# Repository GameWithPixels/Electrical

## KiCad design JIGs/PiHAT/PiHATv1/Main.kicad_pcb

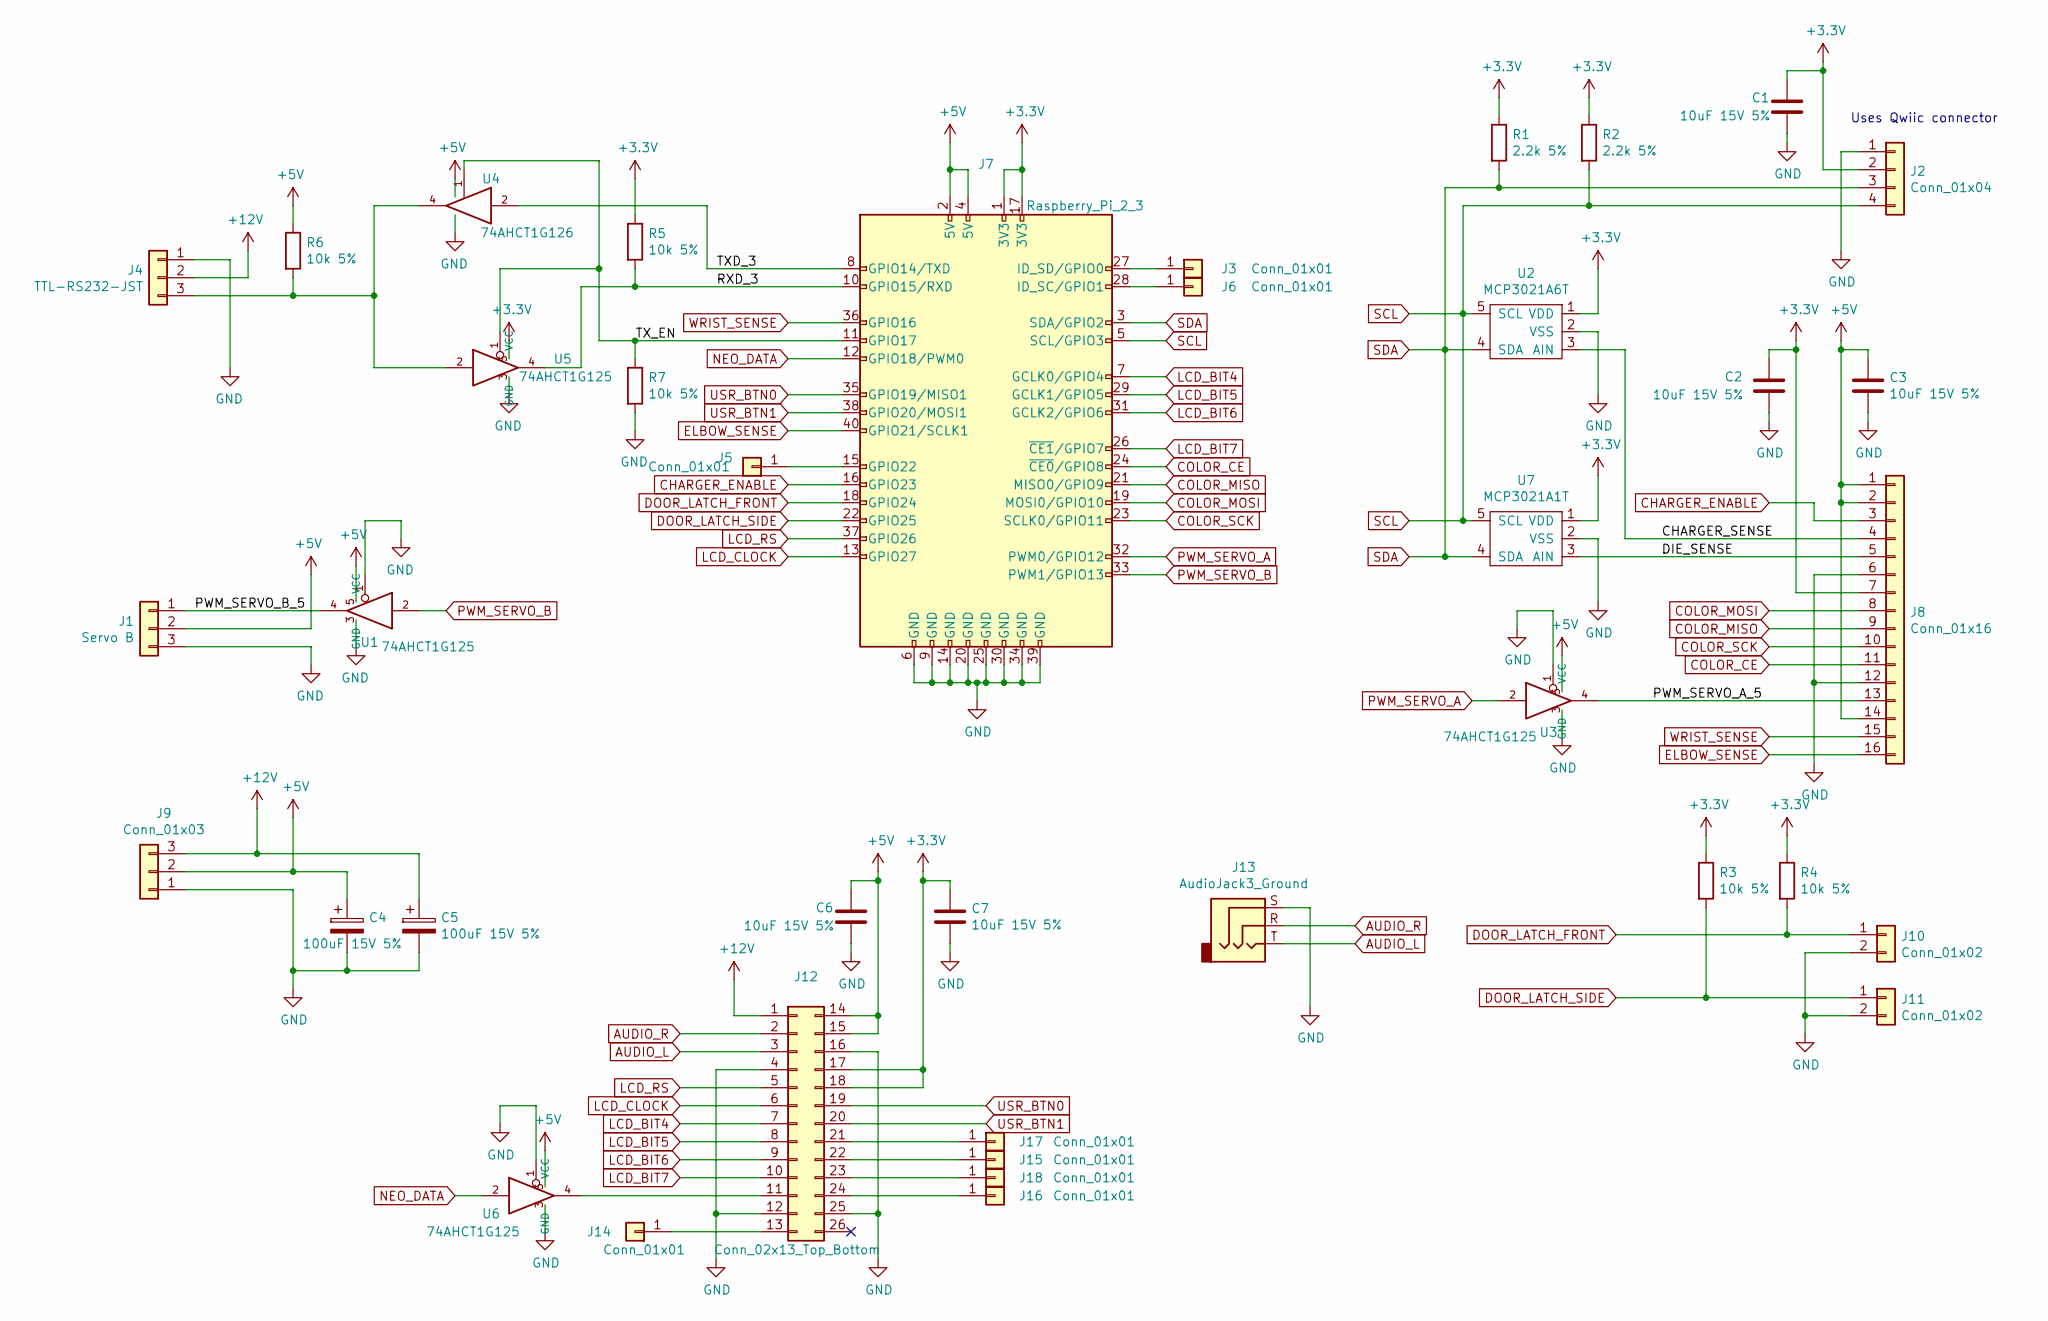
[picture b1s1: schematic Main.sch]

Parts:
C1, C2, C3, C6, C7: 10uF 15V 5%; C_0805_2012Metric; Mouser PN 81-GRM21BR61C106KE5K
C4, C5: 100uF 15V 5%; CP_EIA-7343-43_Kemet-X; Mouser PN 74-293D107X9016D2TE3
J1: Servo B; PinHeader_1x03_P2.54mm_Vertical; Mouser PN 523-G800W305018EU
J2: Conn_01x04; CCSH-W10R-XXTR-BK-A; Part Number CCSH-W10R-XXTR-BK-A
J3, J5, J6, J14, J15, J16, J17, J18: Conn_01x01; TEST_PIN
J4: TTL-RS232-JST; JST_EH_S3B-EH_1x03_P2.50mm_Horizontal; Mouser PN 538-22-05-7035
J7: Raspberry_Pi_2_3; PinSocket_2x20_P2.54mm_Vertical_SMD; Mouser PN 474-PRT-16763
J8: Conn_01x16; PinHeader_2x08_P2.54mm_Vertical_SMD
J9: Conn_01x03; JST_EH_S3B-EH_1x03_P2.50mm_Horizontal; Mouser PN 538-22-05-7035
J10, J11: Conn_01x02; JST_EH_S2B-EH_1x02_P2.50mm_Horizontal; Mouser PN 538-22-05-7025
J12: Conn_02x13_Top_Bottom; PinHeader_2x13_P2.54mm_Vertical_SMD
J13: AudioJack3_Ground; Jack_3.5mm_CUI_SJ1-3533NG_Horizontal_CircularHoles; Mouser PN 490-SJ1-3533NG
R1, R2: 2.2k 5%; R_0603_1608Metric; Mouser PN 603-RC0603FR-072K2L
R3, R4, R5, R6, R7: 10k 5%; R_0603_1608Metric; Mouser PN 603-RC0603FR-1010KL
U1, U3, U5, U6: 74AHCT1G125; SC-74A; Mouser PN 771-AHCT1G125GV125
U2: MCP3021A6T; SOT-23-5; Mouser PN 579-MCP3021A6T-E/OT
U4: 74AHCT1G126; SC-74A; Mouser PN 771-AHCT1G126GV125
U7: MCP3021A1T; SOT-23-5; Mouser PN 579-MCP3021A1T-E/OT

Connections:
+3V3: C1.1, C2.1, C7.1, J2.2, J7.1 (3V3), J7.17 (3V3), J8.7, J12.17, J12.18, R1.1, R2.1, R3.1, R4.1, R5.1, U2.1 (VDD), U5.5 (VCC), U7.1 (VDD)
+5V: C3.1, C4.1, C6.1, J1.2, J7.2 (5V), J7.4 (5V), J8.1, J8.2, J8.14, J9.2, J12.14, J12.15, R6.1, U1.5 (VCC), U3.5 (VCC), U4.5 (VCC), U6.5 (VCC)
+12V: C5.1, J4.2, J9.3, J12.1
/CHARGER_SENSE: J8.4, U2.3 (AIN)
/DIE_SENSE: J8.5, U7.3 (AIN)
/NEOPIXEL_DATA: J4.3, R6.2, U4.4, U5.2
/PWM_SERVO_A_5: J8.13, U3.4
/PWM_SERVO_B_5: J1.1, U1.4
/RXD_3: J7.10 (GPIO15/RXD), R5.2, U5.4
/TXD_3: J7.8 (GPIO14/TXD), U4.2
/TX_EN: J7.11 (GPIO17), R7.1, U4.1, U5.1
AUDIO_L: J12.3, J13.T
AUDIO_R: J12.2, J13.R
CHARGER_ENABLE: J7.16 (GPIO23), J8.3
COLOR_CE: J7.24 (~CE0~/GPIO8), J8.11
COLOR_MISO: J7.21 (MISO0/GPIO9), J8.9
COLOR_MOSI: J7.19 (MOSI0/GPIO10), J8.8
COLOR_SCK: J7.23 (SCLK0/GPIO11), J8.10
DOOR_LATCH_FRONT: J7.18 (GPIO24), J10.1, R4.2
DOOR_LATCH_SIDE: J7.22 (GPIO25), J11.1, R3.2
ELBOW_SENSE: J7.40 (GPIO21/SCLK1), J8.16
GND: C1.2, C2.2, C3.2, C4.2, C5.2, C6.2, C7.2, J1.3, J2.1, J4.1, J7.6 (GND), J7.9 (GND), J7.14 (GND), J7.20 (GND), J7.25 (GND), J7.30 (GND), J7.34 (GND), J7.39 (GND), J8.6, J8.12, J9.1, J10.2, J11.2, J12.4, J12.12, J12.16, J12.25, J13.S, R7.2, U1.1, U1.3 (GND), U2.2 (VSS), U3.1, U3.3 (GND), U4.3 (GND), U5.3 (GND), U6.1, U6.3 (GND), U7.2 (VSS)
LCD_BIT4: J7.7 (GCLK0/GPIO4), J12.7
LCD_BIT5: J7.29 (GCLK1/GPIO5), J12.8
LCD_BIT6: J7.31 (GCLK2/GPIO6), J12.9
LCD_BIT7: J7.26 (~CE1~/GPIO7), J12.10
LCD_CLOCK: J7.13 (GPIO27), J12.6
LCD_RS: J7.37 (GPIO26), J12.5
NEO_DATA: J7.12 (GPIO18/PWM0), U6.2
unnamed: J3.1, J7.27 (ID_SD/GPIO0)
unnamed: J5.1, J7.15 (GPIO22)
unnamed: J6.1, J7.28 (ID_SC/GPIO1)
unnamed: J12.11, U6.4
unnamed: J12.13, J14.1
unnamed: J12.21, J17.1
unnamed: J12.22, J15.1
unnamed: J12.23, J18.1
unnamed: J12.24, J16.1
PWM_SERVO_A: J7.32 (PWM0/GPIO12), U3.2
PWM_SERVO_B: J7.33 (PWM1/GPIO13), U1.2
SCL: J2.4, J7.5 (SCL/GPIO3), R2.2, U2.5 (SCL), U7.5 (SCL)
SDA: J2.3, J7.3 (SDA/GPIO2), R1.2, U2.4 (SDA), U7.4 (SDA)
USR_BTN0: J7.35 (GPIO19/MISO1), J12.19
USR_BTN1: J7.38 (GPIO20/MOSI1), J12.20
WRIST_SENSE: J7.36 (GPIO16), J8.15

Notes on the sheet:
Uses Qwiic connector

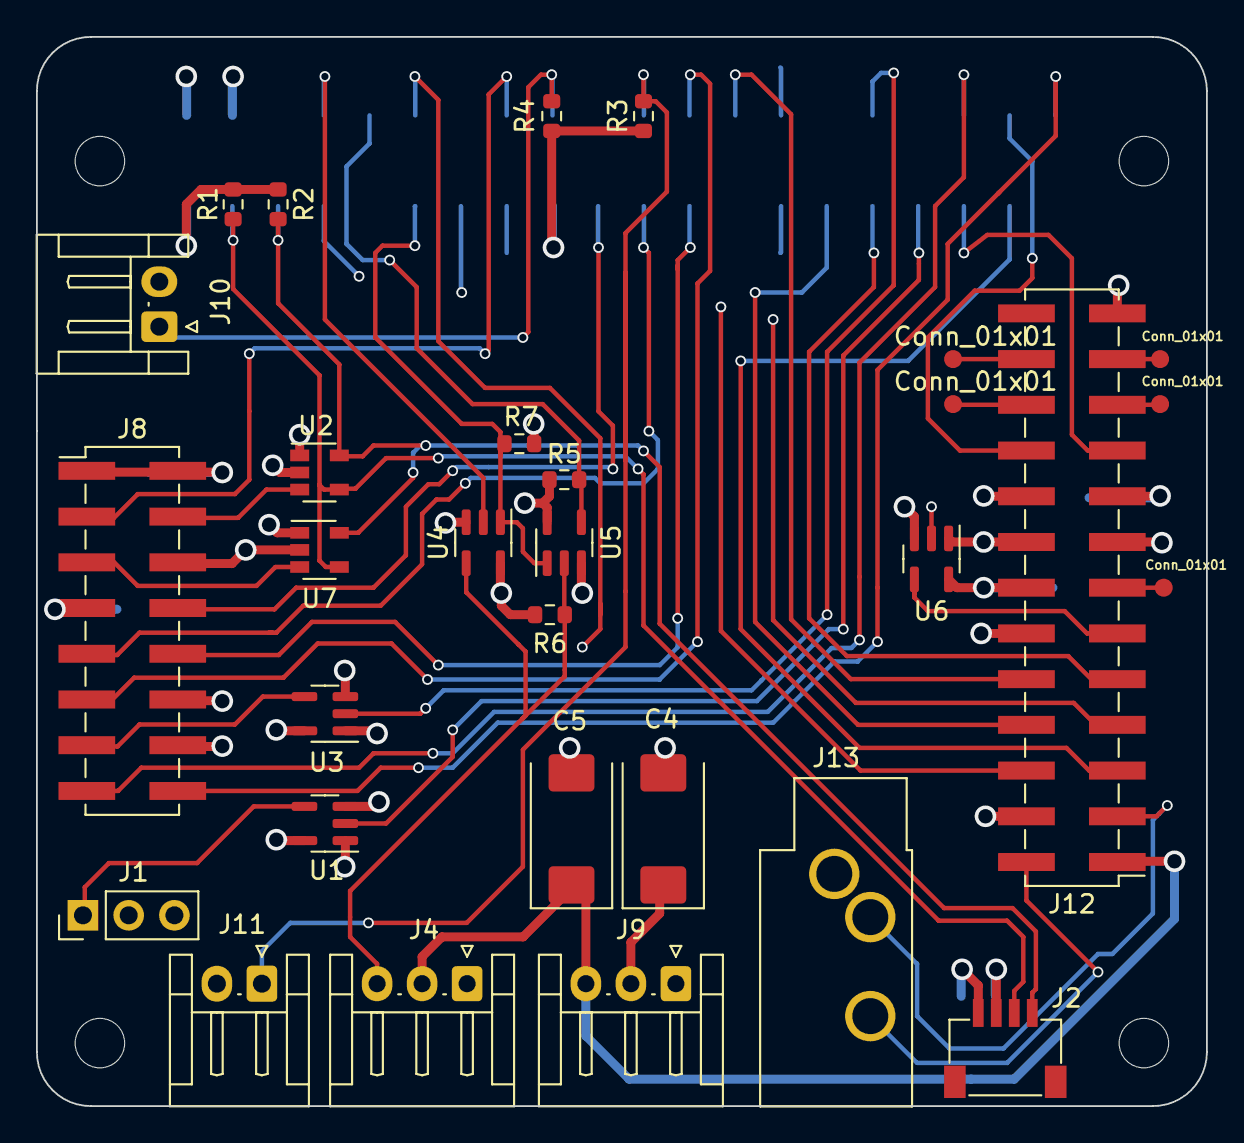
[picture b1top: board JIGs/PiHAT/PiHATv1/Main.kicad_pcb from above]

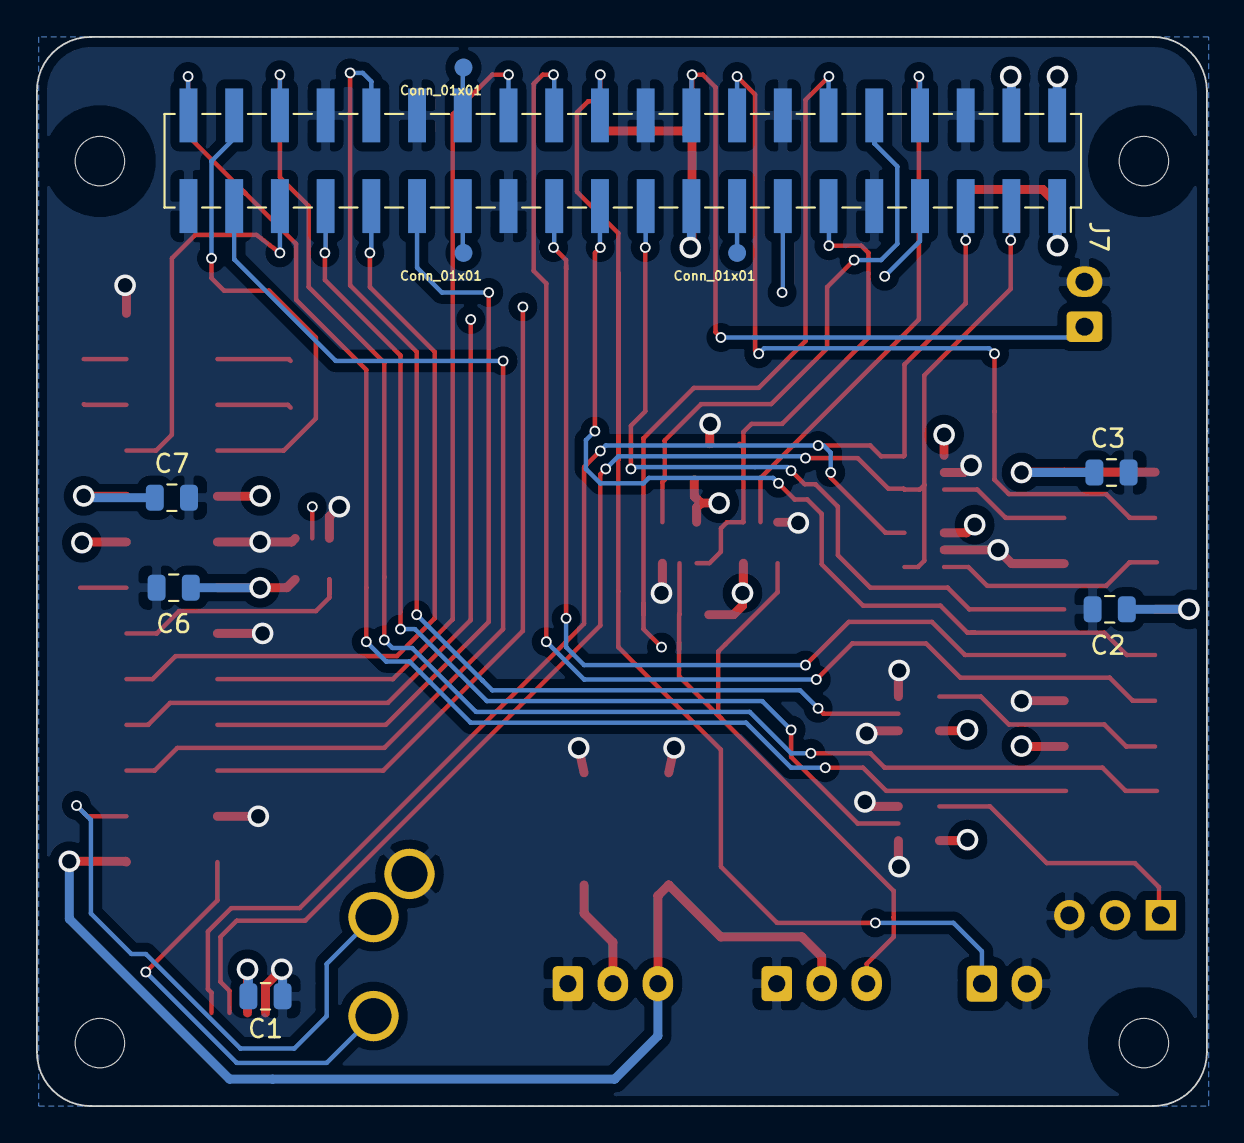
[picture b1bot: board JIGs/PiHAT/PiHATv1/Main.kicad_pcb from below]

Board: 4 copper layers, 65.0 x 59.4 mm, 39 parts (9 on the bottom side), 45 nets.

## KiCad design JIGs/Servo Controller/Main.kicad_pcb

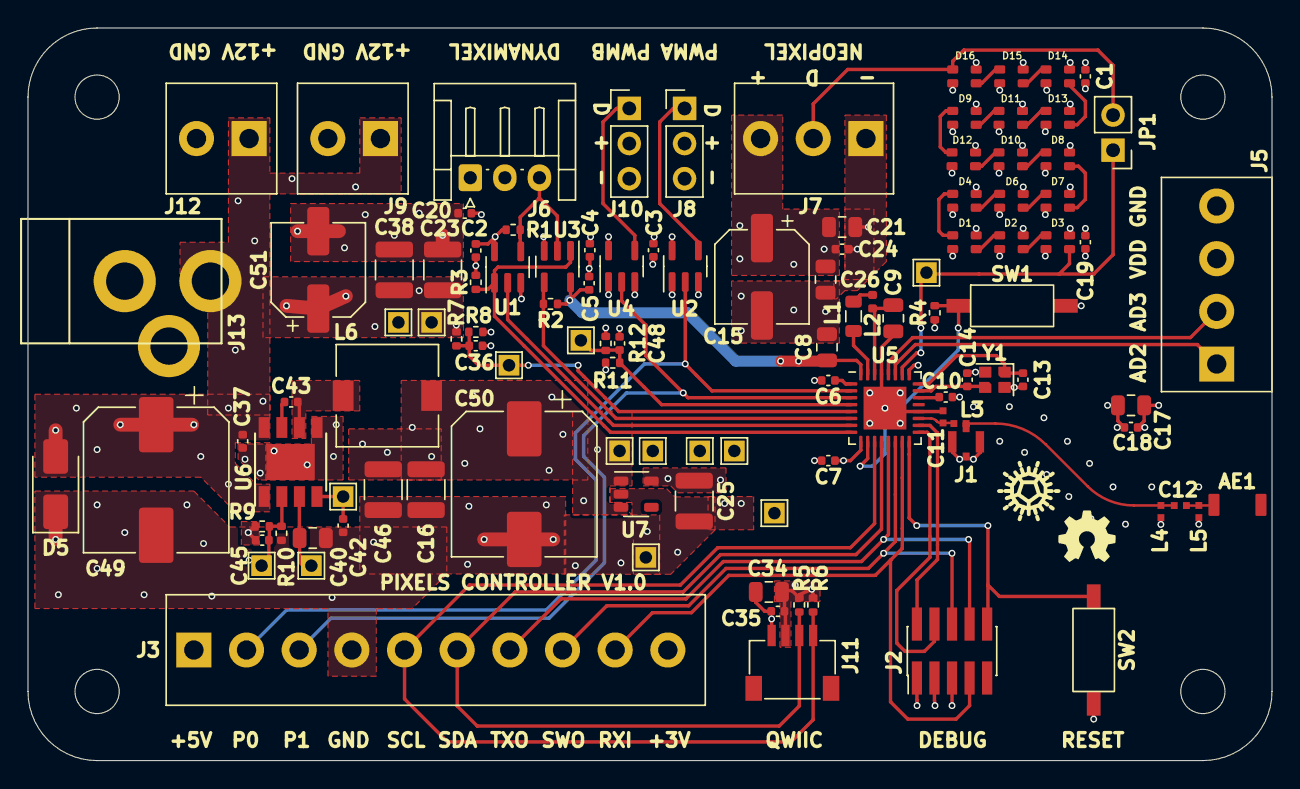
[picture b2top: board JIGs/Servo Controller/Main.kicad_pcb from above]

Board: 4 copper layers, 90.0 x 53.0 mm, 115 parts (0 on the bottom side), 56 nets.

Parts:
AE1: Antenna_Chip; CHIP_ANT
C1, C2, C3, C4, C5, C6, C7, C18, C19, C20, C24, C35, C37, C43: 0.1uF 25V; C_0402_1005Metric
C8, C9, C17, C21, C26, C34, C40: 10uF 10V; C_0805_2012Metric
C10: 100pF NP0 10V 5%; C_0402_1005Metric
C11: 0.8pF 10V 5% NP0; 0402_RF
C12: DNP; 0402_RF
C13, C14: 8pF 10V 10%; C_0402_1005Metric
C15, C51: 100uF 50V; CP_Elec_6.3x5.4
C16, C23, C25, C38, C46: 22uF 25V; C_1210_3225Metric
C36, C48: 10nF 50V; C_0402_1005Metric
C42: 8200pF 16V; C_0402_1005Metric
C45: 10pF 10V 20%; C_0402_1005Metric
C49, C50: 220uF 50V; CP_Elec_10x10
D1, D2, D3, D4, D6, D7, D8, D9, D10, D11, D12, D13, D14, D15, D16: TX1812Z_2020
D5: D_TVS; D_SMA
H1, H2, H3, H4: MountingHole; MountingHole_3.2mm_M3
J1: DNP; MFH3.RECE.20369.001E.01
J2: Conn_02x05_Odd_Even; PinHeader_2x05_P1.27mm_Vertical_SMD
J3: Screw_Terminal_01x10; DB125-3.81-10P-GN-S
J5: Screw_Terminal_01x04; DB125-3.81-4P-GN-S
J6: DYNAMIXEL; JST_EH_S3B-EH_1x03_P2.50mm_Horizontal
J7: Neopixel; DB125-3.81-3P-GN-S
J8: SERVOA; PinHeader_1x03_P2.54mm_Vertical
J9, J12: Screw_Terminal_01x02; DB125-3.81-2P-GN-S
J10: SERVOB; PinHeader_1x03_P2.54mm_Vertical
J11: Qwiic; CCSH-W10R-XXTR-BK-A
J13: Barrel_Jack_Switch; BARREL_JACK
JP1: Jumper_2_Open; PinHeader_1x02_P2.54mm_Vertical
L1: 10uH 100mA; L_0805_2012Metric
L2: 15nH; L_0402_1005Metric
L3: 3.9nH 5%; 0402_RF
L4, L5: 10nH 5%; 0402_RF
L6: 3.3uH 6A; L_7.3x7.3_H3.5
R1, R2, R3, R4: 10k 5%; R_0402_1005Metric
R5, R6: 2.2k 5%; R_0402_1005Metric
R7, R11, R12: 4.02M 1%; R_0402_1005Metric
R8: 1M 1%; R_0402_1005Metric
R9: 124k 1%; R_0402_1005Metric
R10: 22.1k 1%; R_0402_1005Metric
SW1, SW2: SW_Push; TSB008A2530A
U1: 74AHCT1G126; SC-74A
U2, U3, U4: 74AHCT1G125; SC-74A
U5: N52810_QFN32; QFN-32-1EP_5x5mm_P0.5mm_EP3.1x3.1mm
U6: TPS54627; Diodes_SO-8EP
U7: ME6215; SOT-23-5
W1: LED_DATA1; TestPoint_1.5x1.5_Drill0.9mm
W2, W3, W4, W5, W7: GND; TestPoint_1.5x1.5_Drill0.9mm
W6: 12V_SENSE; TestPoint_1.5x1.5_Drill0.9mm
W8: +12V; TestPoint_1.5x1.5_Drill0.9mm
W9: VREG5; TestPoint_1.5x1.5_Drill0.9mm
W10: SS; TestPoint_1.5x1.5_Drill0.9mm
W11: VDD; TestPoint_1.5x1.5_Drill0.9mm
W12: FB; TestPoint_1.5x1.5_Drill0.9mm
W13: +5VD; TestPoint_1.5x1.5_Drill0.9mm
W14: 5V_SENSE; TestPoint_1.5x1.5_Drill0.9mm
Y1: 32MHz 40ppm; Crystal_SMD_2016-4Pin_2.0x1.6mm

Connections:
+5VD: C1.1, C2.1, C3.1, C4.1, C15.1, C16.1, C19.1, C21.1, C24.1, C26.1, C45.1, C46.1, C50.1, D1.2 (VCC), D2.2 (VCC), D3.2 (VCC), D4.2 (VCC), D6.2 (VCC), D7.2 (VCC), D8.2 (VCC), D9.2 (VCC), D10.2 (VCC), D11.2 (VCC), D12.2 (VCC), D13.2 (VCC), D14.2 (VCC), D15.2 (VCC), D16.2 (VCC), J3.1, J7.3, J8.2, J10.2, L6.2, R1.1, R9.2, R11.1, U1.5 (VCC), U2.5 (VCC), U4.5 (VCC), U7.1 (VIN), U7.3 (CE), W13.1
+12V: C20.1, C23.1, C37.1, C38.1, C49.1, C51.1, D5.2 (A2), J6.2, J9.1, J12.1, J13.1, R7.1, U6.1 (EN), U6.8 (VIN), W8.1
/5V_SENSE: C48.1, R11.2, R12.1, U5.4 (P0.04/AIN2), W14.1
/12V_SENSE: C36.1, R7.2, R8.1, U5.5 (P0.05/AIN3), W6.1
/ANTENNA: AE1.1 (FEED), L4.2, L5.1
/ANT_50: C12.1, J1.4 (RF), L3.2, L4.1
/ANT_NRF: C11.1, L3.1, U5.19 (ANT)
/BTN: R4.2, SW1.1, U5.10 (P0.12)
/Connectors/AIN2: J5.1, U5.27 (P0.28/AIN4)
/Connectors/AIN3: J5.2, U5.28 (P0.30/AIN6)
/Connectors/DYNAMIXEL: J6.3, R1.2, U1.4, U3.2
/Connectors/NEOPIXEL: D16.3 (DOUT), J7.2, JP1.2 (B)
/Connectors/SERVOA: J8.1, U2.4
/Connectors/SERVOB: J10.1, U4.4
/LEDs/LED_IN: D3.1 (DIN), JP1.1 (A), U5.26 (P0.25), W1.1
/RESET: J2.10, SW2.1, U5.16 (P0.16)
/RXD_3: R2.2, U3.4, U5.6 (P0.06)
/RXI: J2.7, J3.9, U5.15 (P0.20/TCLK)
/SCL: J3.5, J11.4, R6.2, U5.11 (P0.14)
/SDA: J3.6, J11.3, R5.2, U5.12 (P0.15)
/SERVOA_3: J3.2, U2.2, U5.2 (P0.00/XL1)
/SERVOB_3: J3.3, U4.2, U5.3 (P0.01/XL2)
/SWDCLK: J2.4, U5.17 (SWDCLK)
/SWDIO: J2.2, U5.18 (SWDIO)
/SWO: J2.6, J3.8, U5.14 (P0.18/TDATA0)
/TXD_3: U1.2, U5.7 (P0.09)
/TXO: J2.8, J3.7, U5.13 (P0.16/TDATA1)
/TX_EN: R3.1, U1.1, U3.1, U5.8 (P0.10)
GND: C1.2, C2.2, C3.2, C4.2, C5.2, C6.2, C7.2, C8.2, C9.2, C10.2, C11.2, C12.2, C13.1, C14.1, C15.2, C16.2, C17.2, C18.2, C19.2, C20.2, C21.2, C23.2, C24.2, C25.2, C26.2, C34.2, C35.2, C36.2, C37.2, C38.2, C40.2, C42.2, C46.2, C48.2, C49.2, C50.2, C51.2, D1.4 (GND), D2.4 (GND), D3.4 (GND), D4.4 (GND), D5.1 (A1), D6.4 (GND), D7.4 (GND), D8.4 (GND), D9.4 (GND), D10.4 (GND), D11.4 (GND), D12.4 (GND), D13.4 (GND), D14.4 (GND), D15.4 (GND), D16.4 (GND), J1.1, J1.2, J1.3, J2.3, J2.5, J3.4, J5.4, J6.1, J7.1, J8.3, J9.2, J10.3, J11.1, J12.2, J13.2, J13.3, L5.2, R3.2, R8.2, R10.1, R12.2, SW1.2, SW2.2, U1.3 (GND), U2.1, U2.3 (GND), U3.3 (GND), U4.1, U4.3 (GND), U5.20 (VSS), U5.29 (VSS), U5.33 (VSS), U6.5 (GND), U6.9 (PwPd), U7.2 (VSS), W2.1, W3.1, W4.1, W5.1, W7.1, Y1.2, Y1.4
unnamed: D1.1 (DIN), D2.3 (DOUT)
unnamed: D1.3 (DOUT), D4.1 (DIN)
unnamed: D2.1 (DIN), D3.3 (DOUT)
unnamed: D4.3 (DOUT), D6.1 (DIN)
unnamed: D6.3 (DOUT), D7.1 (DIN)
unnamed: D7.3 (DOUT), D8.1 (DIN)
unnamed: D8.3 (DOUT), D10.1 (DIN)
unnamed: D10.3 (DOUT), D12.1 (DIN)
unnamed: D9.3 (DOUT), D11.1 (DIN)
unnamed: D11.3 (DOUT), D13.1 (DIN)
unnamed: D9.1 (DIN), D12.3 (DOUT)
unnamed: D13.3 (DOUT), D14.1 (DIN)
unnamed: D14.3 (DOUT), D15.1 (DIN)
unnamed: D15.3 (DOUT), D16.1 (DIN)
unnamed: L1.2, L2.1
unnamed: L1.1, U5.31 (DCC)
unnamed: C6.1, U5.1 (DEC1)
unnamed: C10.1, U5.22 (DEC3)
unnamed: C9.1, L2.2, U5.30 (DEC4)
unnamed: C14.2, U5.23 (XC1), Y1.3
unnamed: C13.2, U5.24 (XC2), Y1.1
unnamed: C42.1, U6.4 (SS), W10.1
unnamed: C43.2, L6.1, U6.6 (SW)
unnamed: C43.1, U6.7 (VBST)
unnamed: C45.2, R9.1, R10.2, U6.2 (VFB), W12.1
unnamed: C40.1, U6.3 (VREG5), W9.1
VDD: C5.1, C7.1, C8.1, C17.1, C18.1, C25.1, C34.1, C35.1, J2.1, J3.10, J5.3, J11.2, R2.1, R4.1, R5.1, R6.1, U3.5 (VCC), U5.9 (VDD), U5.25 (VDD), U5.32 (VDD), U7.5 (VOUT), W11.1

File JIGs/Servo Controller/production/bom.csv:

Designator,Footprint,Quantity,Value,LCSC Part #
AE1,CHIP_ANT,1,Antenna_Chip,C486319
"C1, C18, C19, C2, C20, C24, C3, C35, C37, C4, C43, C5, C6, C7",0402,14,0.1uF 25V,C105883
C10,0402,1,100pF NP0 10V 5%,C147476
C11,0402_RF,1,0.8pF 10V 5% NP0,C76915
"C13, C14",0402,2,8pF 10V 10%,C521082
"C15, C51",CP_Elec_6.3x5.4,2,100uF 50V,C97807
"C16, C23, C25, C38, C46",1210,5,22uF 25V,C12891
"C17, C21, C26, C34, C40, C8, C9",0805,7,10uF 10V,C1713
"C36, C48",0402,2,10nF 50V,C386111
C42,0402,1,8200pF 16V,C309459
C45,0402,1,10pF 10V 20%,C2168196
"C49, C50",CP_Elec_10x10,2,220uF 50V,C125977
"D1, D10, D11, D12, D13, D14, D15, D16, D2, D3, D4, D6, D7, D8, D9",TX1812Z_2020,15,TX1812Z_2020,C784564
D5,D_SMA,1,D_TVS,C148217
"H1, H2, H3, H4",MountingHole_3.2mm_M3,4,MountingHole,
J10,PinHeader_1x03_P2.54mm_Vertical,1,SERVOB,C2894926
J11,CCSH-W10R-XXTR-BK-A,1,Qwiic,
"J12, J9",DB125-3.81-2P-GN-S,2,Screw_Terminal_01x02,C395878
J13,BARREL_JACK,1,Barrel_Jack_Switch,C7507454
J2,PinHeader_2x05_P1.27mm_Vertical_SMD,1,Conn_02x05_Odd_Even,C2962219
J3,DB125-3.81-10P-GN-S,1,Screw_Terminal_01x10,C5137189
J5,DB125-3.81-4P-GN-S,1,Screw_Terminal_01x04,C395880
J6,JST_EH_S3B-EH_1x03_P2.50mm_Horizontal,1,DYNAMIXEL,C185225
J7,DB125-3.81-3P-GN-S,1,Neopixel,C395879
J8,PinHeader_1x03_P2.54mm_Vertical,1,SERVOA,C2894926
JP1,PinHeader_1x02_P2.54mm_Vertical,1,Jumper_2_Open,
L1,0805,1,10uH 100mA,C223269
L2,0402,1,15nH,C97979
L3,0402_RF,1,3.9nH 5%,C5452416
"L4, L5",0402_RF,2,10nH 5%,C77103
L6,L_7.3x7.3_H3.5,1,3.3uH 6A,C514807
"R1, R2, R3, R4",0402,4,10k 5%,C25744
R10,0402,1,22.1k 1%,C43473
"R11, R12, R7",0402,3,4.02M 1%,C423177
"R5, R6",0402,2,2.2k 5%,C25879
R8,0402,1,1M 1%,C26083
R9,0402,1,124k 1%,C36777
"SW1, SW2",TSB008A2530A,2,SW_Push,C2888954
U1,SC-74A,1,74AHCT1G126,C842288
"U2, U3, U4",SC-74A,3,74AHCT1G125,C12494
U5,QFN-32-1EP_5x5mm_P0.5mm_EP3.1x3.1mm,1,N52810_QFN32,
U6,Diodes_SO-8EP,1,TPS54627,C398919
U7,SOT-23-5,1,ME6215,C236664
W1,TestPoint_1.5x1.5_Drill0.9mm,1,LED_DATA1,
W10,TestPoint_1.5x1.5_Drill0.9mm,1,SS,
W11,TestPoint_1.5x1.5_Drill0.9mm,1,VDD,
W12,TestPoint_1.5x1.5_Drill0.9mm,1,FB,
W13,TestPoint_1.5x1.5_Drill0.9mm,1,+5VD,
W14,TestPoint_1.5x1.5_Drill0.9mm,1,5V_SENSE,
"W2, W3, W4, W5, W7",TestPoint_1.5x1.5_Drill0.9mm,5,GND,
W6,TestPoint_1.5x1.5_Drill0.9mm,1,12V_SENSE,
W8,TestPoint_1.5x1.5_Drill0.9mm,1,+12V,
W9,TestPoint_1.5x1.5_Drill0.9mm,1,VREG5,
Y1,Crystal_SMD_2016-4Pin_2.0x1.6mm,1,32MHz 40ppm,C527602

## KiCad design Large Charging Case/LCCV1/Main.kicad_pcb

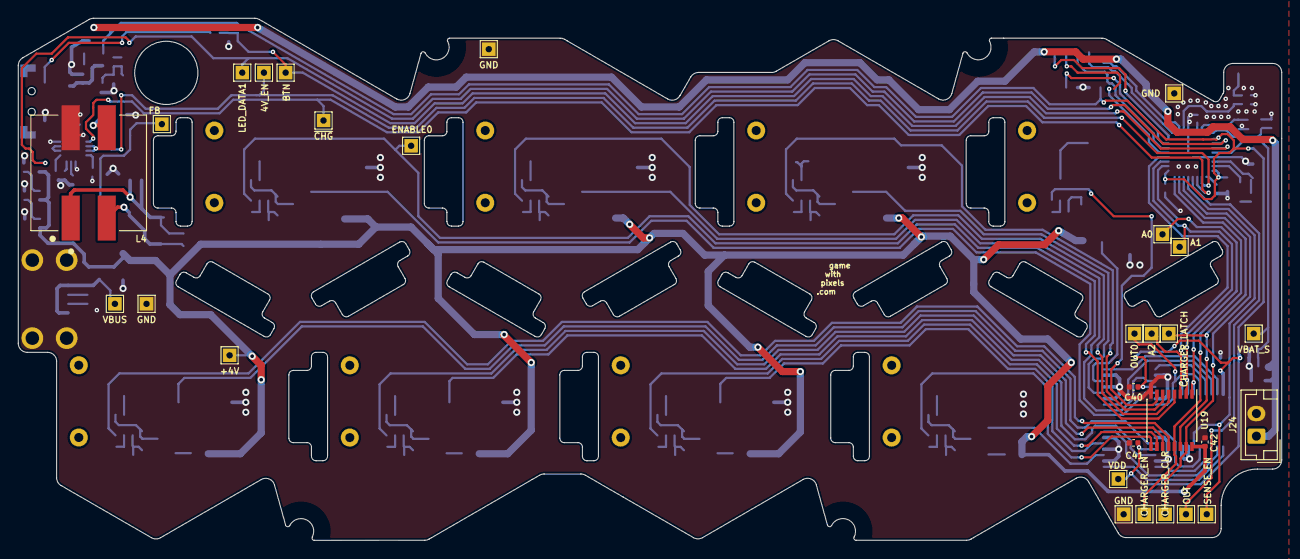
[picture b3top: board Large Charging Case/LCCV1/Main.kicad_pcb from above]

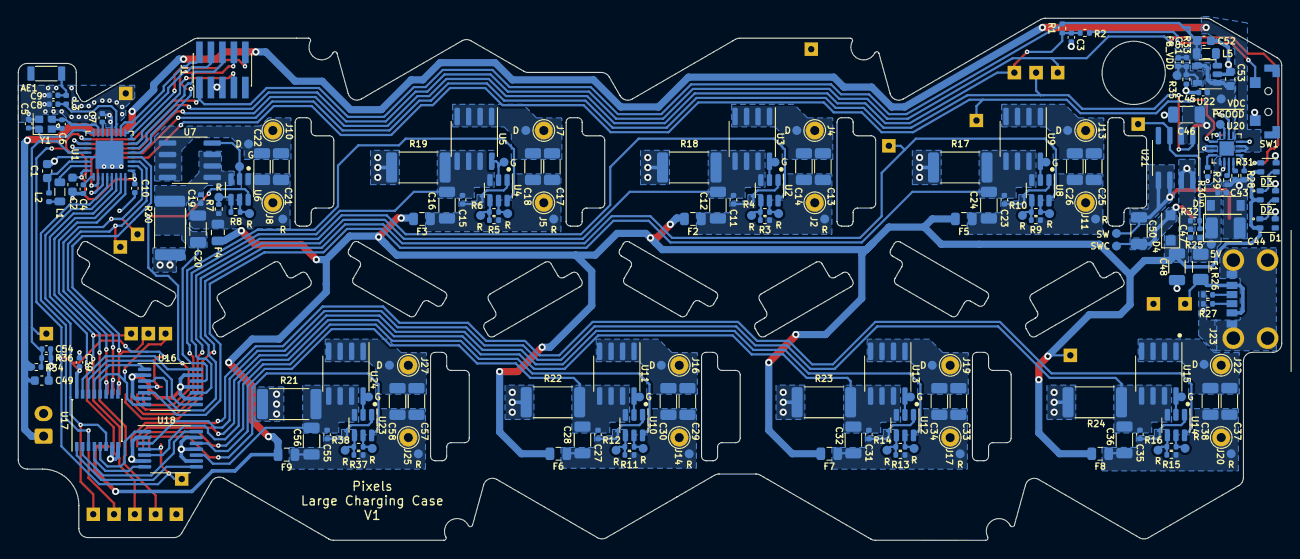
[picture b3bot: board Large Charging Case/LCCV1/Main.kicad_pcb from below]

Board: 2 copper layers, 139.9 x 57.8 mm, 238 parts (201 on the bottom side), 114 nets.

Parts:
AE1: ChipAnt; CHIP_ANT
C1, C2, C49, C52, C53: 4.7uF 6.3V 20%; C_0603_1608Metric
C3, C4, C10, C11, C15, C19, C23, C27, C31, C35, C39, C40, C41, C42, C43, C45, C47, C55: 0.1uF 10V 20%; C_0402_1005Metric
C5, C6: 6pF 10V 10%; C_0402_1005Metric
C7: 100pF NP0 10V 5%; C_0402_1005Metric
C8: 1.5pF 10V NP0; C_0402_1005Metric
C9: DNP; C_0402_1005Metric
C12, C16, C20, C24, C28, C32, C36, C46, C48, C50, C56: 47uF 10V 20%; C_1206_3216Metric
C13, C17, C21, C25, C29, C33, C37, C57: 100nF 50V NP0; C_1206_3216Metric
C14, C18, C22, C26, C30, C34, C38, C58: 56nF 50V NP0; C_1206_3216Metric
C44: 220uF 10V 20% Tantalum; CP_EIA-3528-21_Kemet-B
C51: 22pF 10V 5%; C_0402_1005Metric
C54: 10nF 25V 10%; C_0402_1005Metric
D1, D2, D3: TX1812Z_2020
D4: 30V 2A; D_SOD-123F
D5: 5.1V 1500mW; D_SOD-123
F1: 1500mA <150mR; Fuse_1206_3216Metric
F2, F3, F4, F5, F6, F7, F8, F9: 500mA ~150mR; Fuse_0805_2012Metric
J1: Conn_02x05_Odd_Even; PinHeader_2x05_P1.27mm_Vertical_SMD
J2, J5, J8, J11, J14, J17, J20, J25: Coil B; TestPoint_THTPad_D2.0mm_Drill1.0mm
J3, J6, J9, J12, J15, J18, J21, J26: TX_Coil; TX Coil
J4, J7, J10, J13, J16, J19, J22, J27: Coil A; TestPoint_THTPad_D2.0mm_Drill1.0mm
J23: USB_C_Receptacle_USB2.0; USB-C-SMD_10P-P1.00-L6.8-W8.9
J24: Conn_01x02; JST_EH_B2B-EH-A_1x02_P2.50mm_Vertical
L1: 10uH 100mA 10%; L_0805_2012Metric
L2: 15nH; L_0402_1005Metric
L3: 3.9nH; L_0402_1005Metric
L4: 22uH 2A 20%; Murata 4700
L5: 2.2uH 20mA 10%; L_0805_2012Metric
R1, R28: 10k 5%; R_0402_1005Metric
R2, R30: 1k 1%; R_0402_1005Metric
R3, R5, R7, R9, R11, R13, R15, R37: 200k 1%; R_0402_1005Metric
R4, R6, R8, R10, R12, R14, R16, R38: 84.5k 1%; R_0402_1005Metric
R17, R18, R19, R20, R21, R22, R23, R24: 30mR 2W 1%; R_2512_6332Metric
R25: 8.66k 1%; R_0402_1005Metric
R26, R27: 5.1k 1%; R_0402_1005Metric
R29: 3k 1%; R_0402_1005Metric
R31: 1.8k 1%; R_0402_1005Metric
R32: 3.32k 1%; R_0402_1005Metric
R33: 402k 1%; R_0402_1005Metric
R34: 4.02M 1%; R_0402_1005Metric
R35: 100k 1%; R_0402_1005Metric
R36: 10M 1%; R_0402_1005Metric
SW1: SW_Push; TSB001
U1: N52810_QFN32; QFN-32-1EP_5x5mm_P0.5mm_EP3.1x3.1mm
U2, U4, U6, U8, U10, U12, U14, U23: XKT001; SOT-23-6
U3, U5, U7, U9, U11, U13, U15, U24: XKT335; SOIC-8_3.9x4.9mm_P1.27mm
U16, U18: INA4180A4; TSSOP-14_4.4x5mm_P0.65mm
U17: DG4051E; SSOP-16_4.4x5.2mm_P0.65mm
U19: 74HCT259; SSOP-16_4.4x5.2mm_P0.65mm
U20: BQ24232H; VQFN-16-1EP_3x3mm_P0.5mm_EP1.6x1.6mm
U21: XL6007E1; SOIC-8_3.9x4.9mm_P1.27mm
U22: LN3406; SOT-23-5
W1: LED_DATA1; TestPoint_THTPad_1.5x1.5mm_Drill0.7mm
W2, W3, W44, W45: GND; TestPoint_THTPad_1.5x1.5mm_Drill0.7mm
W4, W5, W8, W9, W10, W13, W14, W15, W18, W19, W20, W23, W24, W25, W28, W29, W30, W33, W34, W35, W38, W71, W72, W75: R; TEST_PIN
W6, W11, W16, W21, W26, W31, W36, W73: G; TEST_PIN
W7, W12, W17, W22, W27, W32, W37, W74: D; TEST_PIN
W39: ENABLE0; TestPoint_THTPad_1.5x1.5mm_Drill0.7mm
W40: OUT0; TestPoint_THTPad_1.5x1.5mm_Drill0.7mm
W41: A2; TestPoint_THTPad_1.5x1.5mm_Drill0.7mm
W42: A1; TestPoint_THTPad_1.5x1.5mm_Drill0.7mm
W43: A0; TestPoint_THTPad_1.5x1.5mm_Drill0.7mm
W47: OUT; TestPoint_THTPad_1.5x1.5mm_Drill0.7mm
W48: SENSE_EN; TestPoint_THTPad_1.5x1.5mm_Drill0.7mm
W57: CHARGER_EN; TestPoint_THTPad_1.5x1.5mm_Drill0.7mm
W58: CHARGER_LATCH; TestPoint_THTPad_1.5x1.5mm_Drill0.7mm
W59: CHARGER_CLR; TestPoint_THTPad_1.5x1.5mm_Drill0.7mm
W60: ~{PGOOD}; TEST_PIN
W61: VBUS; TestPoint_THTPad_1.5x1.5mm_Drill0.7mm
W62: 5V; TEST_PIN
W63: VDC; TEST_PIN
W64: SWC; TEST_PIN
W65: +4V; TestPoint_THTPad_1.5x1.5mm_Drill0.7mm
W66: SW; TEST_PIN
W67: FB; TestPoint_THTPad_1.5x1.5mm_Drill0.7mm
W68: VDD; TestPoint_THTPad_1.5x1.5mm_Drill0.7mm
W69: FB_VDD; TEST_PIN
W70: VBAT_S; TestPoint_THTPad_1.5x1.5mm_Drill0.7mm
W76: BTN; TestPoint_THTPad_1.5x1.5mm_Drill0.7mm
W78: ~{CHG}; TestPoint_THTPad_1.5x1.5mm_Drill0.7mm
W79: 4V_EN; TestPoint_THTPad_1.5x1.5mm_Drill0.7mm
Y1: 32MHz 40ppm; Crystal_SMD_2016-4Pin_2.0x1.6mm

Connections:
+4V: C42.1, C47.1, C48.1, D1.2 (VCC), D2.2 (VCC), D3.2 (VCC), D4.1 (K), F2.1, F3.1, F4.1, F5.1, F6.1, F7.1, F8.1, F9.1, R25.1, U19.16 (VCC), W65.1
+5V: C43.1, C44.1, D5.1 (K), F1.2, U20.13 (IN), W62.1
+BATT: C49.1, J24.1, R34.1, U20.2 (BAT), U20.3 (BAT)
+VDC: C45.1, C46.1, C53.1, L4.3, U20.5 (EN2), U20.10 (OUT), U20.11 (OUT), U21.2 (VIN), U22.1 (CE), U22.4 (VIN), W63.1
/Multiplexed Chargers/CHARGER_ENL_D: U1.8 (P0.10), U19.13 (D), W57.1
/Multiplexed Chargers/CHARGER_SELECT_A0: U1.10 (P0.12), U17.11 (A), U19.1 (A0), W43.1
/Multiplexed Chargers/CHARGER_SELECT_A1: U1.11 (P0.14), U17.10 (B), U19.2 (A1), W42.1
/Multiplexed Chargers/CHARGER_SELECT_A2: U1.12 (P0.15), U17.9 (C), U19.3 (A2), W41.1
/Multiplexed Chargers/Charger 1/CHARGER_GND: C23.2, C24.2, R17.2, U8.3 (GND), U9.5 (S), U9.6 (S), U9.7 (S), U16.5 (IN+)
/Multiplexed Chargers/Charger 2/CHARGER_GND: C11.2, C12.2, R18.2, U2.3 (GND), U3.5 (S), U3.6 (S), U3.7 (S), U16.3 (IN+)
/Multiplexed Chargers/Charger 3/CHARGER_GND: C15.2, C16.2, R19.2, U4.3 (GND), U5.5 (S), U5.6 (S), U5.7 (S), U16.10 (IN+)
/Multiplexed Chargers/Charger 4/CHARGER_GND: C19.2, C20.2, R20.2, U6.3 (GND), U7.5 (S), U7.6 (S), U7.7 (S), U16.12 (IN+)
/Multiplexed Chargers/Charger 5/CHARGER_GND: C55.2, C56.2, R21.2, U18.10 (IN+), U23.3 (GND), U24.5 (S), U24.6 (S), U24.7 (S)
/Multiplexed Chargers/Charger 6/CHARGER_GND: C27.2, C28.2, R22.2, U10.3 (GND), U11.5 (S), U11.6 (S), U11.7 (S), U18.12 (IN+)
/Multiplexed Chargers/Charger 7/CHARGER_GND: C31.2, C32.2, R23.2, U12.3 (GND), U13.5 (S), U13.6 (S), U13.7 (S), U18.5 (IN+)
/Multiplexed Chargers/Charger 8/CHARGER_GND: C35.2, C36.2, R24.2, U14.3 (GND), U15.5 (S), U15.6 (S), U15.7 (S), U18.3 (IN+)
/Multiplexed Chargers/ENABLE0: U8.6 (N/F), U19.4 (Q0), W39.1
/Multiplexed Chargers/ENABLE1: U2.6 (N/F), U19.5 (Q1)
/Multiplexed Chargers/ENABLE2: U4.6 (N/F), U19.6 (Q2)
/Multiplexed Chargers/ENABLE3: U6.6 (N/F), U19.7 (Q3)
/Multiplexed Chargers/ENABLE4: U19.9 (Q4), U23.6 (N/F)
/Multiplexed Chargers/ENABLE5: U10.6 (N/F), U19.10 (Q5)
/Multiplexed Chargers/ENABLE6: U12.6 (N/F), U19.11 (Q6)
/Multiplexed Chargers/ENABLE7: U14.6 (N/F), U19.12 (Q7)
/Multiplexed Chargers/SENSE0: U16.1 (OUT), U17.13 (X0)
/Multiplexed Chargers/SENSE1: U16.8 (OUT), U17.14 (X1)
/Multiplexed Chargers/SENSE2: U16.14 (OUT), U17.15 (X2)
/Multiplexed Chargers/SENSE3: U16.7 (OUT), U17.12 (X3), W40.1
/Multiplexed Chargers/SENSE4: U17.1 (X4), U18.8 (OUT)
/Multiplexed Chargers/SENSE5: U17.5 (X5), U18.1 (OUT)
/Multiplexed Chargers/SENSE6: U17.2 (X6), U18.14 (OUT)
/Multiplexed Chargers/SENSE7: U17.4 (X7), U18.7 (OUT)
/Multiplexed Chargers/SENSE_EN: U1.5 (P0.05/AIN3), U17.6 (ENABLE), W48.1
/Multiplexed Chargers/SENSE_OUT: U1.4 (P0.04/AIN2), U17.3 (X), W47.1
/Multiplexed Chargers/~CHARGER_ENL_CLR: U1.6 (P0.06), U19.15 (Clr), W59.1
/Multiplexed Chargers/~CHARGER_ENL_EN: U1.7 (P0.09), U19.14 (E), W58.1
/Power/4V_EN: U1.2 (P0.00/XL1), U21.1 (EN), W79.1
/Power/VBAT_SENSE: C54.1, R34.2, R36.1, U1.28 (P0.30/AIN6), W70.1
/Power/~CHG: U1.3 (P0.01/XL2), U20.9 (~CHG), W78.1
GND: C1.2, C2.2, C3.2, C4.2, C5.1, C6.1, C7.2, C8.1, C9.2, C10.2, C39.2, C40.2, C41.2, C42.2, C43.2, C44.2, C45.2, C46.2, C47.2, C48.2, C49.2, C52.2, C53.2, C54.2, D1.4 (GND), D2.4 (GND), D3.4 (GND), D5.2 (A), J1.3, J1.5, J23.A12 (GND), J23.B12 (GND), J23.S1 (SHIELD), J24.2, L4.4, R17.1, R18.1, R19.1, R20.1, R21.1, R22.1, R23.1, R24.1, R26.1, R27.1, R28.2, R29.2, R30.2, R31.2, R32.2, R35.1, R36.2, SW1.2, U1.20 (VSS), U1.29 (VSS), U1.33 (VSS), U16.2 (IN-), U16.6 (IN-), U16.9 (IN-), U16.11 (GND), U16.13 (IN-), U17.7 (V-), U17.8 (GND), U18.2 (IN-), U18.6 (IN-), U18.9 (IN-), U18.11 (GND), U18.13 (IN-), U19.8 (GND), U20.4 (~CE), U20.6 (EN1), U20.8 (VSS), U20.14 (TMR), U21.7 (GND), U21.8 (GND), U22.2 (GND), W2.1, W3.1, W44.1, W45.1, Y1.2, Y1.4
unnamed: AE1.1 (A), C9.1, L3.2
unnamed: C1.1, L2.2, U1.30 (DEC4)
unnamed: C3.1, R1.1, R2.2, U1.27 (P0.28/AIN4), W76.1
unnamed: C4.1, U1.1 (DEC1)
unnamed: C5.2, U1.24 (XC2), Y1.1
unnamed: C6.2, U1.23 (XC1), Y1.3
unnamed: C7.1, U1.22 (DEC3)
unnamed: C8.2, L3.1, U1.19 (ANT)
unnamed: C11.1, C12.1, C13.2, C14.2, F2.2, J2.1, R3.2, U2.1 (VDD), W4.1
unnamed: C13.1, C14.1, J4.1, U3.1 (D), U3.2 (D), U3.3 (D), U3.4 (D), W7.1
unnamed: C15.1, C16.1, C17.2, C18.2, F3.2, J5.1, R5.2, U4.1 (VDD), W9.1
unnamed: C17.1, C18.1, J7.1, U5.1 (D), U5.2 (D), U5.3 (D), U5.4 (D), W12.1
unnamed: C19.1, C20.1, C21.2, C22.2, F4.2, J8.1, R7.2, U6.1 (VDD), W14.1
unnamed: C21.1, C22.1, J10.1, U7.1 (D), U7.2 (D), U7.3 (D), U7.4 (D), W17.1
unnamed: C23.1, C24.1, C25.2, C26.2, F5.2, J11.1, R9.2, U8.1 (VDD), W19.1
unnamed: C25.1, C26.1, J13.1, U9.1 (D), U9.2 (D), U9.3 (D), U9.4 (D), W22.1
unnamed: C27.1, C28.1, C29.2, C30.2, F6.2, J14.1, R11.2, U10.1 (VDD), W24.1
unnamed: C29.1, C30.1, J16.1, U11.1 (D), U11.2 (D), U11.3 (D), U11.4 (D), W27.1
unnamed: C31.1, C32.1, C33.2, C34.2, F7.2, J17.1, R13.2, U12.1 (VDD), W29.1
unnamed: C33.1, C34.1, J19.1, U13.1 (D), U13.2 (D), U13.3 (D), U13.4 (D), W32.1
unnamed: C35.1, C36.1, C37.2, C38.2, F8.2, J20.1, R15.2, U14.1 (VDD), W34.1
unnamed: C37.1, C38.1, J22.1, U15.1 (D), U15.2 (D), U15.3 (D), U15.4 (D), W37.1
unnamed: C50.1, L4.1, U21.5 (SW), U21.6 (SW), W66.1
unnamed: C50.2, D4.2 (A), L4.2, W64.1
unnamed: C51.2, R33.1, R35.2, U22.5 (FB), W69.1
unnamed: C55.1, C56.1, C57.2, C58.2, F9.2, J25.1, R37.2, U23.1 (VDD), W71.1
unnamed: C57.1, C58.1, J27.1, U24.1 (D), U24.2 (D), U24.3 (D), U24.4 (D), W74.1
unnamed: D1.1 (DIN), D2.3 (DOUT)
unnamed: D2.1 (DIN), D3.3 (DOUT)
unnamed: D3.1 (DIN), U1.26 (P0.25), W1.1
unnamed: J23.A5 (CC1), R27.2
unnamed: J23.B5 (CC2), R26.2
unnamed: L1.1, U1.31 (DCC)
unnamed: L1.2, L2.1
unnamed: L5.1, U22.3 (LX)
unnamed: R2.1, SW1.1
unnamed: R3.1, R4.1, U2.4 (R), W8.1
unnamed: R4.2, U2.5 (R), W5.1
unnamed: R5.1, R6.1, U4.4 (R), W13.1
unnamed: R6.2, U4.5 (R), W10.1
unnamed: R7.1, R8.1, U6.4 (R), W18.1
unnamed: R8.2, U6.5 (R), W15.1
unnamed: R9.1, R10.1, U8.4 (R), W23.1
unnamed: R10.2, U8.5 (R), W20.1
unnamed: R11.1, R12.1, U10.4 (R), W28.1
unnamed: R12.2, U10.5 (R), W25.1
unnamed: R13.1, R14.1, U12.4 (R), W33.1
unnamed: R14.2, U12.5 (R), W30.1
unnamed: R15.1, R16.1, U14.4 (R), W38.1
unnamed: R16.2, U14.5 (R), W35.1
unnamed: R25.2, R32.1, U21.3 (FB), W67.1
unnamed: R28.1, U20.1 (TS)
unnamed: R29.1, U20.15 (ITERM)
unnamed: R30.1, U20.12 (ILIM)
unnamed: R31.1, U20.16 (ISET)
unnamed: R37.1, R38.1, U23.4 (R), W75.1
unnamed: R38.2, U23.5 (R), W72.1
unnamed: U2.2 (OUT), U3.8 (G), W6.1
unnamed: U4.2 (OUT), U5.8 (G), W11.1
unnamed: U6.2 (OUT), U7.8 (G), W16.1
unnamed: U8.2 (OUT), U9.8 (G), W21.1
unnamed: U10.2 (OUT), U11.8 (G), W26.1
unnamed: U12.2 (OUT), U13.8 (G), W31.1
unnamed: U14.2 (OUT), U15.8 (G), W36.1
unnamed: U20.7 (~PGOOD), W60.1
unnamed: U23.2 (OUT), U24.8 (G), W73.1
RESET: J1.10, U1.16 (P0.16)
RXI: J1.7, U1.15 (P0.20/TCLK)
SWDCLK: J1.4, U1.17 (SWDCLK)
SWDIO: J1.2, U1.18 (SWDIO)
SWO: J1.6, U1.14 (P0.18/TDATA0)
TXO: J1.8, U1.13 (P0.16/TDATA1)
VBUS: F1.1, J23.A9 (VBUS), J23.B9 (VBUS), W61.1
VDD: C2.1, C10.1, C39.1, C40.1, C41.1, C51.1, C52.1, J1.1, L5.2, R1.2, R33.2, U1.9 (VDD), U1.25 (VDD), U1.32 (VDD), U16.4 (VS), U17.16 (V+), U18.4 (VS), W68.1
